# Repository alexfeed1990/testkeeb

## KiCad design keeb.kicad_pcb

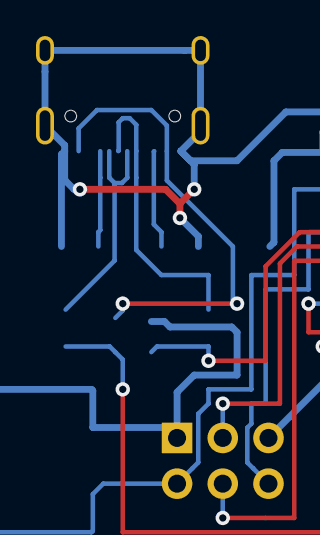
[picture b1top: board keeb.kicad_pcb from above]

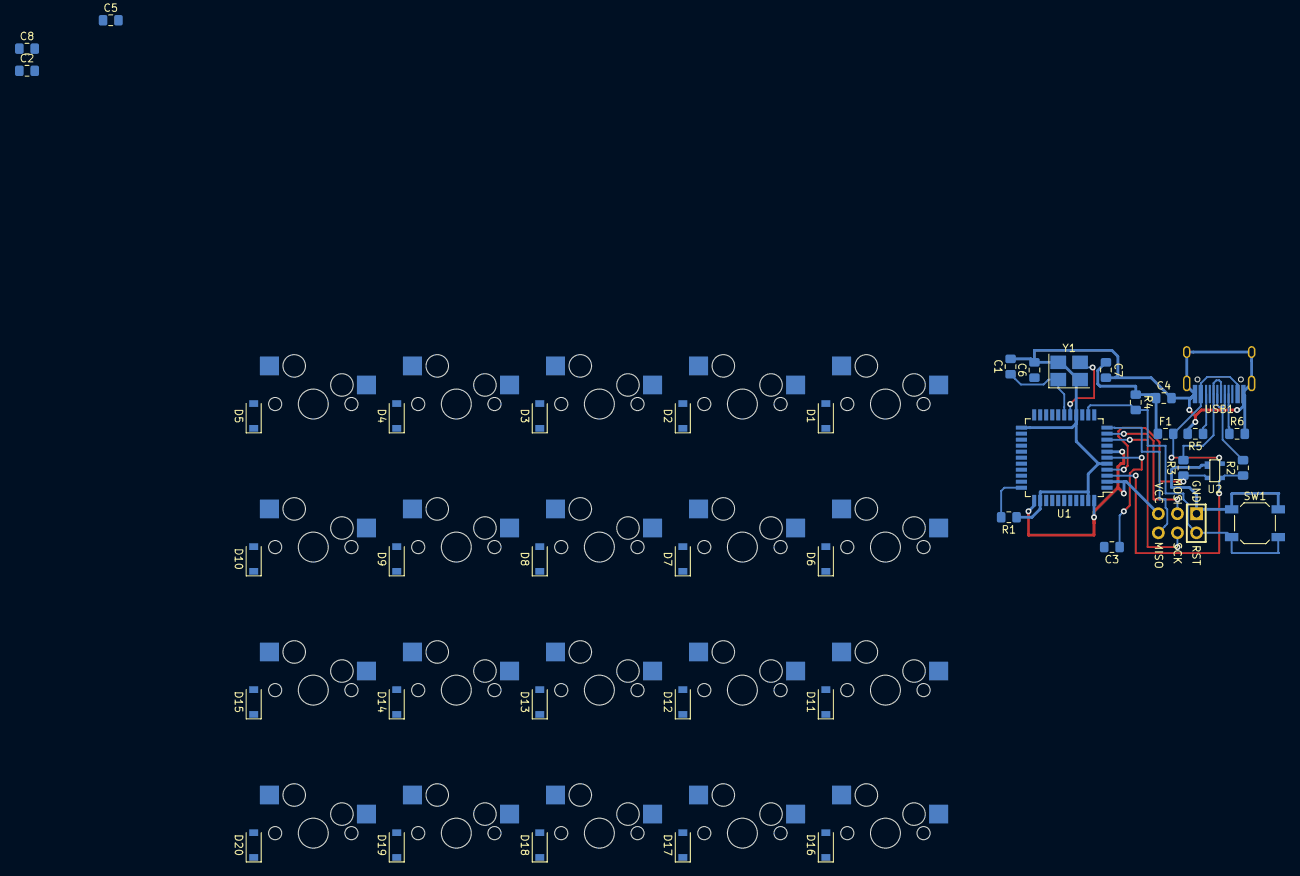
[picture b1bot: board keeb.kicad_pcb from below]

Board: 2 copper layers, 61 parts (41 on the bottom side), 46 nets.

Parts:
C1, C2: 22p; C_0805_2012Metric_Pad1.15x1.40mm_HandSolder
C3: 1u; C_0805_2012Metric_Pad1.15x1.40mm_HandSolder
C4, C5, C6, C7: 0.1u; C_0805_2012Metric_Pad1.15x1.40mm_HandSolder
C8: 10u; C_0805_2012Metric_Pad1.15x1.40mm_HandSolder
D1, D2, D3, D4, D5, D6, D7, D8, D9, D10, D11, D12, D13, D14, D15, D16, D17, D18, D19, D20: D; D_SOD-123
F1: 500m; Fuse_0805_2012Metric_Pad1.15x1.40mm_HandSolder
J1: AVR-ISP-6; Reset_Pretty-Mask
MX1, MX2, MX3, MX4, MX5, MX6, MX7, MX8, MX9, MX10, MX11, MX12, MX13, MX14, MX15, MX16, MX17, MX18, MX19, MX20: MX-NoLED; MXOnly-1U-Hotswap
R1, R4: 10k; R_0805_2012Metric_Pad1.15x1.40mm_HandSolder
R2, R3: 22; R_0805_2012Metric_Pad1.15x1.40mm_HandSolder
R5, R6: 5.1k; R_0805_2012Metric_Pad1.15x1.40mm_HandSolder
SW1: SW_Push; SW_SPST_SKQG_WithStem
U1: ATmega32U4-AU; TQFP-44_10x10mm_P0.8mm
U2: PRTR5V0U2X; SOT143B
USB1: HRO-TYPE-C-31-M-12; HRO-TYPE-C-31-M-12-HandSoldering
Y1: 16MHz; Crystal_SMD_3225-4Pin_3.2x2.5mm_HandSoldering

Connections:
+5V: C4.1, C5.1, C6.1, C7.1, C8.1, F1.1, J1.2, R4.1, U1.2, U1.7, U1.14, U1.24, U1.34, U1.44
COL0: MX1.1, MX6.1, MX11.1, MX16.1
COL1: MX2.1, MX7.1, MX12.1, MX17.1
COL2: MX3.1, MX8.1, MX13.1, MX18.1
COL3: MX4.1, MX9.1, MX14.1, MX19.1
COL4: MX5.1, MX10.1, MX15.1, MX20.1
D+: R3.1, U1.4, U2.2
D-: R2.1, U1.3, U2.3
GND: C1.2, C2.2, C3.2, C4.2, C5.2, C6.2, C7.2, C8.2, J1.6, R1.1, R5.2, R6.2, SW1.1, U1.5, U1.15, U1.23, U1.35, U1.43, U2.1, USB1.1, USB1.12, USB1.13, Y1.2, Y1.4
MISO: J1.1, U1.11
MOSI: J1.4, U1.10
unnamed: C3.1, U1.6
unnamed: D1.2, MX1.2
unnamed: D2.2, MX2.2
unnamed: D3.2, MX3.2
unnamed: D4.2, MX4.2
unnamed: D5.2, MX5.2
unnamed: D6.2, MX6.2
unnamed: D7.2, MX7.2
unnamed: D8.2, MX8.2
unnamed: D9.2, MX9.2
unnamed: D10.2, MX10.2
unnamed: D11.2, MX11.2
unnamed: D12.2, MX12.2
unnamed: D13.2, MX13.2
unnamed: D14.2, MX14.2
unnamed: D15.2, MX15.2
unnamed: D16.2, MX16.2
unnamed: D17.2, MX17.2
unnamed: D18.2, MX18.2
unnamed: D19.2, MX19.2
unnamed: D20.2, MX20.2
unnamed: R1.2, U1.33
unnamed: R2.2, USB1.5, USB1.7
unnamed: R3.2, USB1.6, USB1.8
unnamed: R5.1, USB1.10
unnamed: R6.1, USB1.4
RESET: J1.5, R4.2, SW1.2, U1.13
ROW0: D1.1, D2.1, D3.1, D4.1, D5.1
ROW1: D6.1, D7.1, D8.1, D9.1, D10.1
ROW2: D11.1, D12.1, D13.1, D14.1, D15.1
ROW3: D16.1, D17.1, D18.1, D19.1, D20.1
SCK: J1.3, U1.9
VCC: F1.2, U2.4, USB1.2, USB1.11
XTAL1: C1.1, U1.17, Y1.1
XTAL2: C2.1, U1.16, Y1.3

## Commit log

2023-03-06 Submodules
2023-03-06 uhhh cheeseburger
